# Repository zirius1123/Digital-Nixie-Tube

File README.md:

# Digital-Nixie-Tube
This is a RGB clock that mimics a Nixie Tube clock
## PCB
I used Kicad to design my pcb and schematic

It is a 150 x 275 mm board that is a multi sided polygon. 
## Components
I added 40 SK6812MINI-Es and 6 Cherry MXs. I am using the ESP32-C3-DevKitM-1 for the micro controller.

## Cover
I made the cover in onshape. I made 3 seperate pieces that would serve as the base, cover for the base, and then the cover for the panels.

## Panels
I design the panels from a basic outline that I got from Claude. I used Inkscape to add the tabs and numbers.

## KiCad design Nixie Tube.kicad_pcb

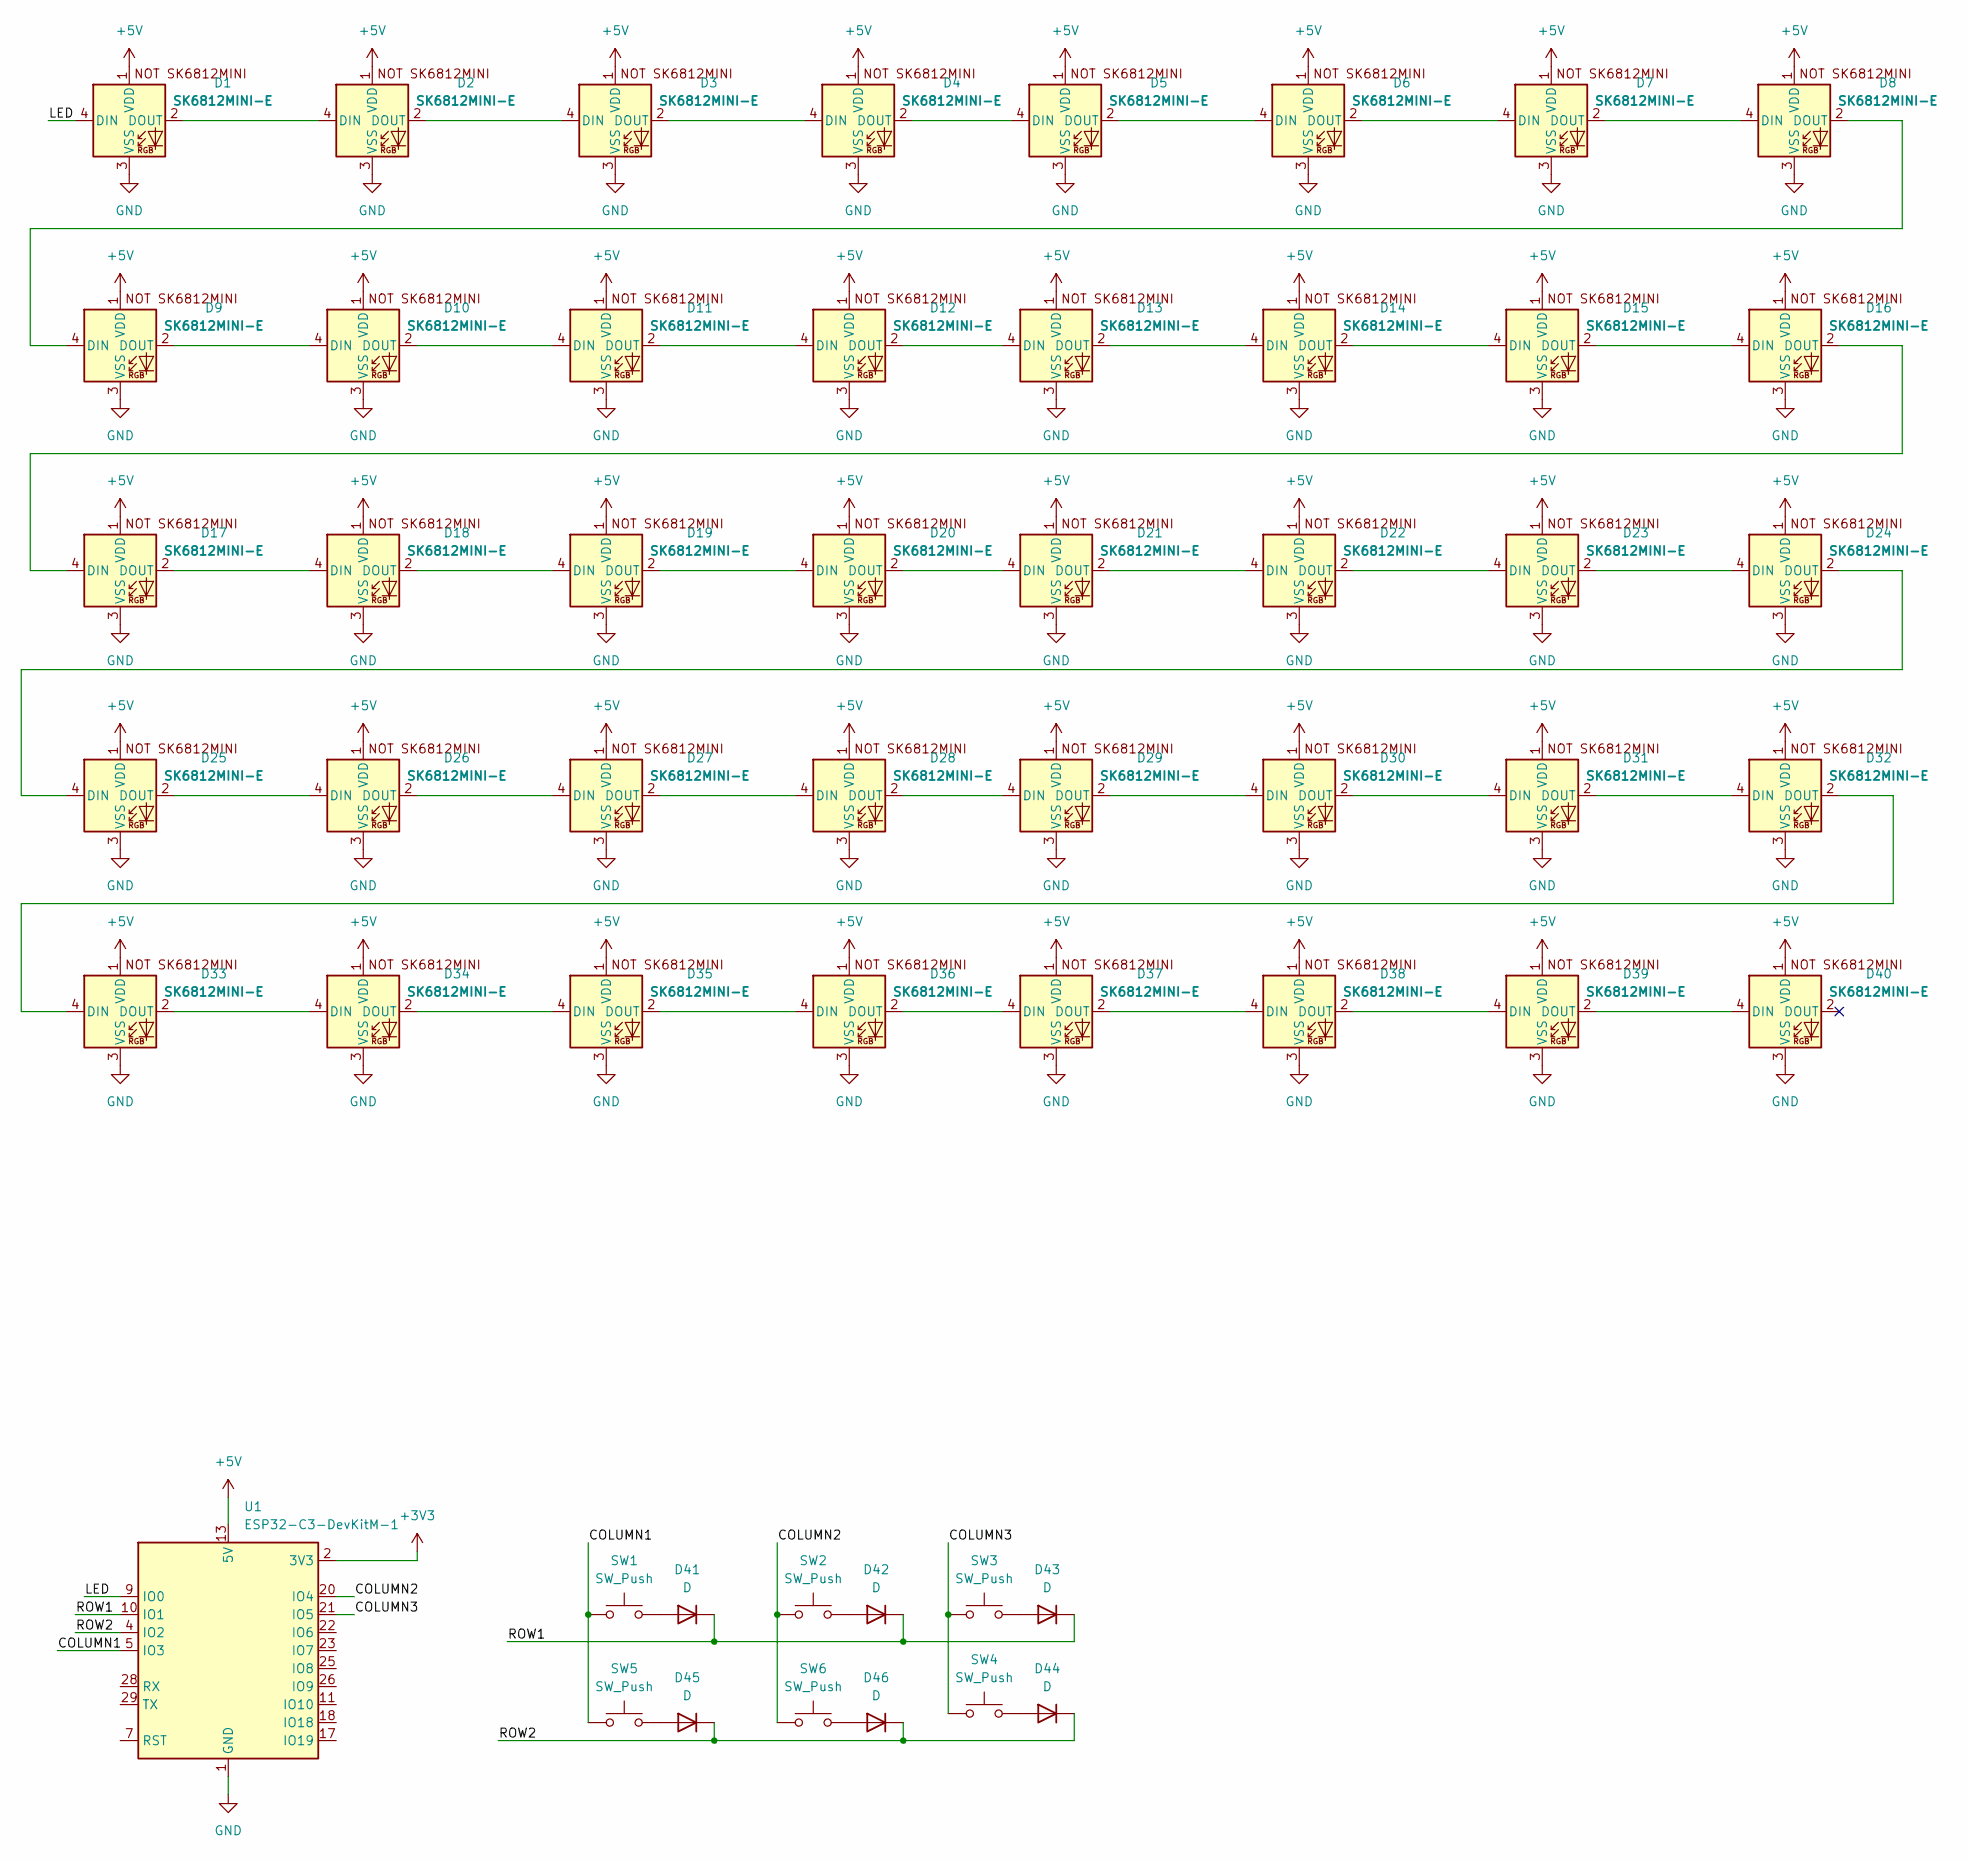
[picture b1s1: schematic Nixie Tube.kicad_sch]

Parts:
D1, D2, D3, D4, D5, D6, D7, D8, D9, D10, D11, D12, D13, D14, D15, D16, D17, D18, D19, D20, D21, D22, D23, D24, D25, D26, D27, D28, D29, D30, D31, D32, D33, D34, D35, D36, D37, D38, D39, D40: SK6812MINI-E; SK6812MINI-E_fixed
D41, D42, D43, D44, D45, D46: D; D_DO-35_SOD27_P7.62mm_Horizontal
SW1, SW2, SW3, SW4, SW5, SW6: SW_Push; SW_Cherry_MX_PCB_1.00u
U1: ESP32-C3-DevKitM-1

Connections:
+3V3: U1.2 (3V3), U1.3 (3V3)
+5V: D1.1 (VDD), D2.1 (VDD), D3.1 (VDD), D4.1 (VDD), D5.1 (VDD), D6.1 (VDD), D7.1 (VDD), D8.1 (VDD), D9.1 (VDD), D10.1 (VDD), D11.1 (VDD), D12.1 (VDD), D13.1 (VDD), D14.1 (VDD), D15.1 (VDD), D16.1 (VDD), D17.1 (VDD), D18.1 (VDD), D19.1 (VDD), D20.1 (VDD), D21.1 (VDD), D22.1 (VDD), D23.1 (VDD), D24.1 (VDD), D25.1 (VDD), D26.1 (VDD), D27.1 (VDD), D28.1 (VDD), D29.1 (VDD), D30.1 (VDD), D31.1 (VDD), D32.1 (VDD), D33.1 (VDD), D34.1 (VDD), D35.1 (VDD), D36.1 (VDD), D37.1 (VDD), D38.1 (VDD), D39.1 (VDD), D40.1 (VDD), U1.13 (5V), U1.14 (5V)
/COLUMN1: SW1.1, SW5.1, U1.5 (IO3)
/COLUMN2: SW2.1, SW6.1, U1.20 (IO4)
/COLUMN3: SW3.1, SW4.1, U1.21 (IO5)
/LED: D1.4 (DIN), U1.9 (IO0)
/ROW1: D41.1 (K), D42.1 (K), D43.1 (K), U1.10 (IO1)
/ROW2: D44.1 (K), D45.1 (K), D46.1 (K), U1.4 (IO2)
GND: D1.3 (VSS), D2.3 (VSS), D3.3 (VSS), D4.3 (VSS), D5.3 (VSS), D6.3 (VSS), D7.3 (VSS), D8.3 (VSS), D9.3 (VSS), D10.3 (VSS), D11.3 (VSS), D12.3 (VSS), D13.3 (VSS), D14.3 (VSS), D15.3 (VSS), D16.3 (VSS), D17.3 (VSS), D18.3 (VSS), D19.3 (VSS), D20.3 (VSS), D21.3 (VSS), D22.3 (VSS), D23.3 (VSS), D24.3 (VSS), D25.3 (VSS), D26.3 (VSS), D27.3 (VSS), D28.3 (VSS), D29.3 (VSS), D30.3 (VSS), D31.3 (VSS), D32.3 (VSS), D33.3 (VSS), D34.3 (VSS), D35.3 (VSS), D36.3 (VSS), D37.3 (VSS), D38.3 (VSS), D39.3 (VSS), D40.3 (VSS), U1.1 (GND), U1.6 (GND), U1.8 (GND), U1.12 (GND), U1.15 (GND), U1.16 (GND), U1.19 (GND), U1.24 (GND), U1.27 (GND), U1.30 (GND)
unnamed: D1.2 (DOUT), D2.4 (DIN)
unnamed: D2.2 (DOUT), D3.4 (DIN)
unnamed: D3.2 (DOUT), D4.4 (DIN)
unnamed: D4.2 (DOUT), D5.4 (DIN)
unnamed: D5.2 (DOUT), D6.4 (DIN)
unnamed: D6.2 (DOUT), D7.4 (DIN)
unnamed: D7.2 (DOUT), D8.4 (DIN)
unnamed: D8.2 (DOUT), D9.4 (DIN)
unnamed: D9.2 (DOUT), D10.4 (DIN)
unnamed: D10.2 (DOUT), D11.4 (DIN)
unnamed: D11.2 (DOUT), D12.4 (DIN)
unnamed: D12.2 (DOUT), D13.4 (DIN)
unnamed: D13.2 (DOUT), D14.4 (DIN)
unnamed: D14.2 (DOUT), D15.4 (DIN)
unnamed: D15.2 (DOUT), D16.4 (DIN)
unnamed: D16.2 (DOUT), D17.4 (DIN)
unnamed: D17.2 (DOUT), D18.4 (DIN)
unnamed: D18.2 (DOUT), D19.4 (DIN)
unnamed: D19.2 (DOUT), D20.4 (DIN)
unnamed: D20.2 (DOUT), D21.4 (DIN)
unnamed: D21.2 (DOUT), D22.4 (DIN)
unnamed: D22.2 (DOUT), D23.4 (DIN)
unnamed: D23.2 (DOUT), D24.4 (DIN)
unnamed: D24.2 (DOUT), D25.4 (DIN)
unnamed: D25.2 (DOUT), D26.4 (DIN)
unnamed: D26.2 (DOUT), D27.4 (DIN)
unnamed: D27.2 (DOUT), D28.4 (DIN)
unnamed: D28.2 (DOUT), D29.4 (DIN)
unnamed: D29.2 (DOUT), D30.4 (DIN)
unnamed: D30.2 (DOUT), D31.4 (DIN)
unnamed: D31.2 (DOUT), D32.4 (DIN)
unnamed: D32.2 (DOUT), D33.4 (DIN)
unnamed: D33.2 (DOUT), D34.4 (DIN)
unnamed: D34.2 (DOUT), D35.4 (DIN)
unnamed: D35.2 (DOUT), D36.4 (DIN)
unnamed: D36.2 (DOUT), D37.4 (DIN)
unnamed: D37.2 (DOUT), D38.4 (DIN)
unnamed: D38.2 (DOUT), D39.4 (DIN)
unnamed: D39.2 (DOUT), D40.4 (DIN)
unnamed: D41.2 (A), SW1.2
unnamed: D42.2 (A), SW2.2
unnamed: D43.2 (A), SW3.2
unnamed: D44.2 (A), SW4.2
unnamed: D45.2 (A), SW5.2
unnamed: D46.2 (A), SW6.2

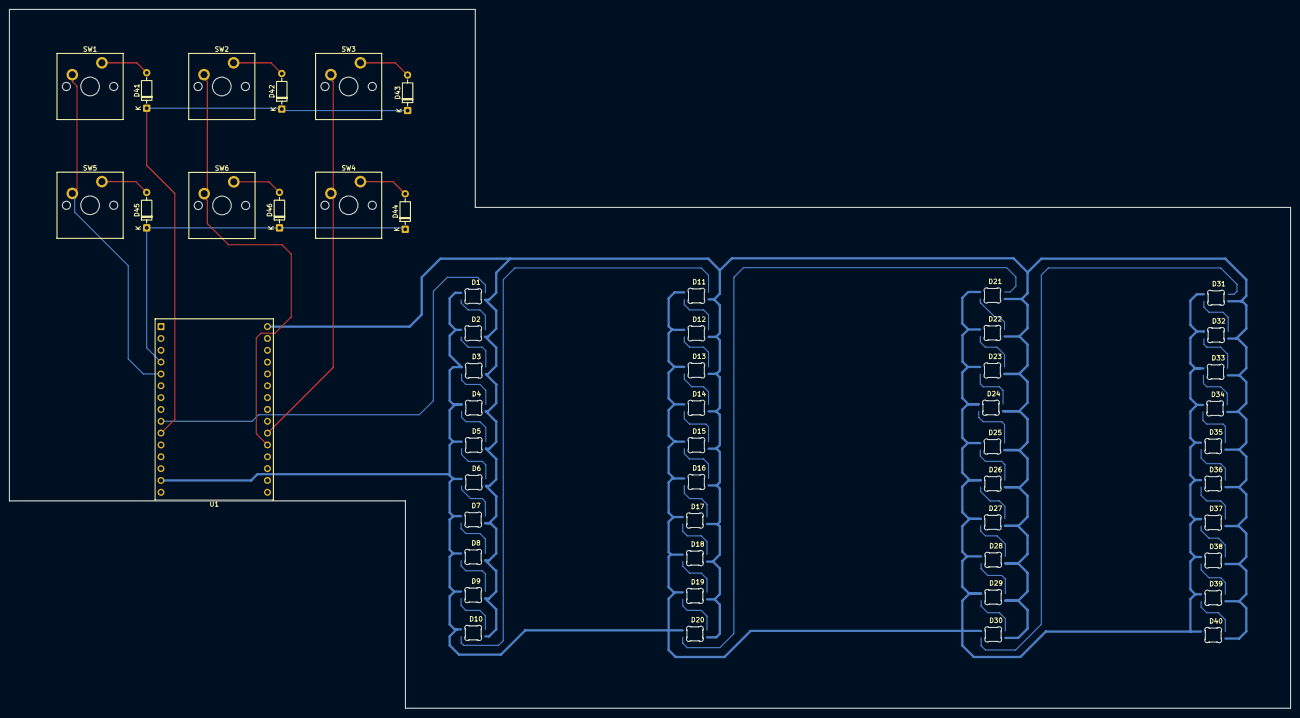
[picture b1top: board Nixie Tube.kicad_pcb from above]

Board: 2 copper layers, 275.0 x 150.0 mm, 53 parts (0 on the bottom side), 54 nets.
